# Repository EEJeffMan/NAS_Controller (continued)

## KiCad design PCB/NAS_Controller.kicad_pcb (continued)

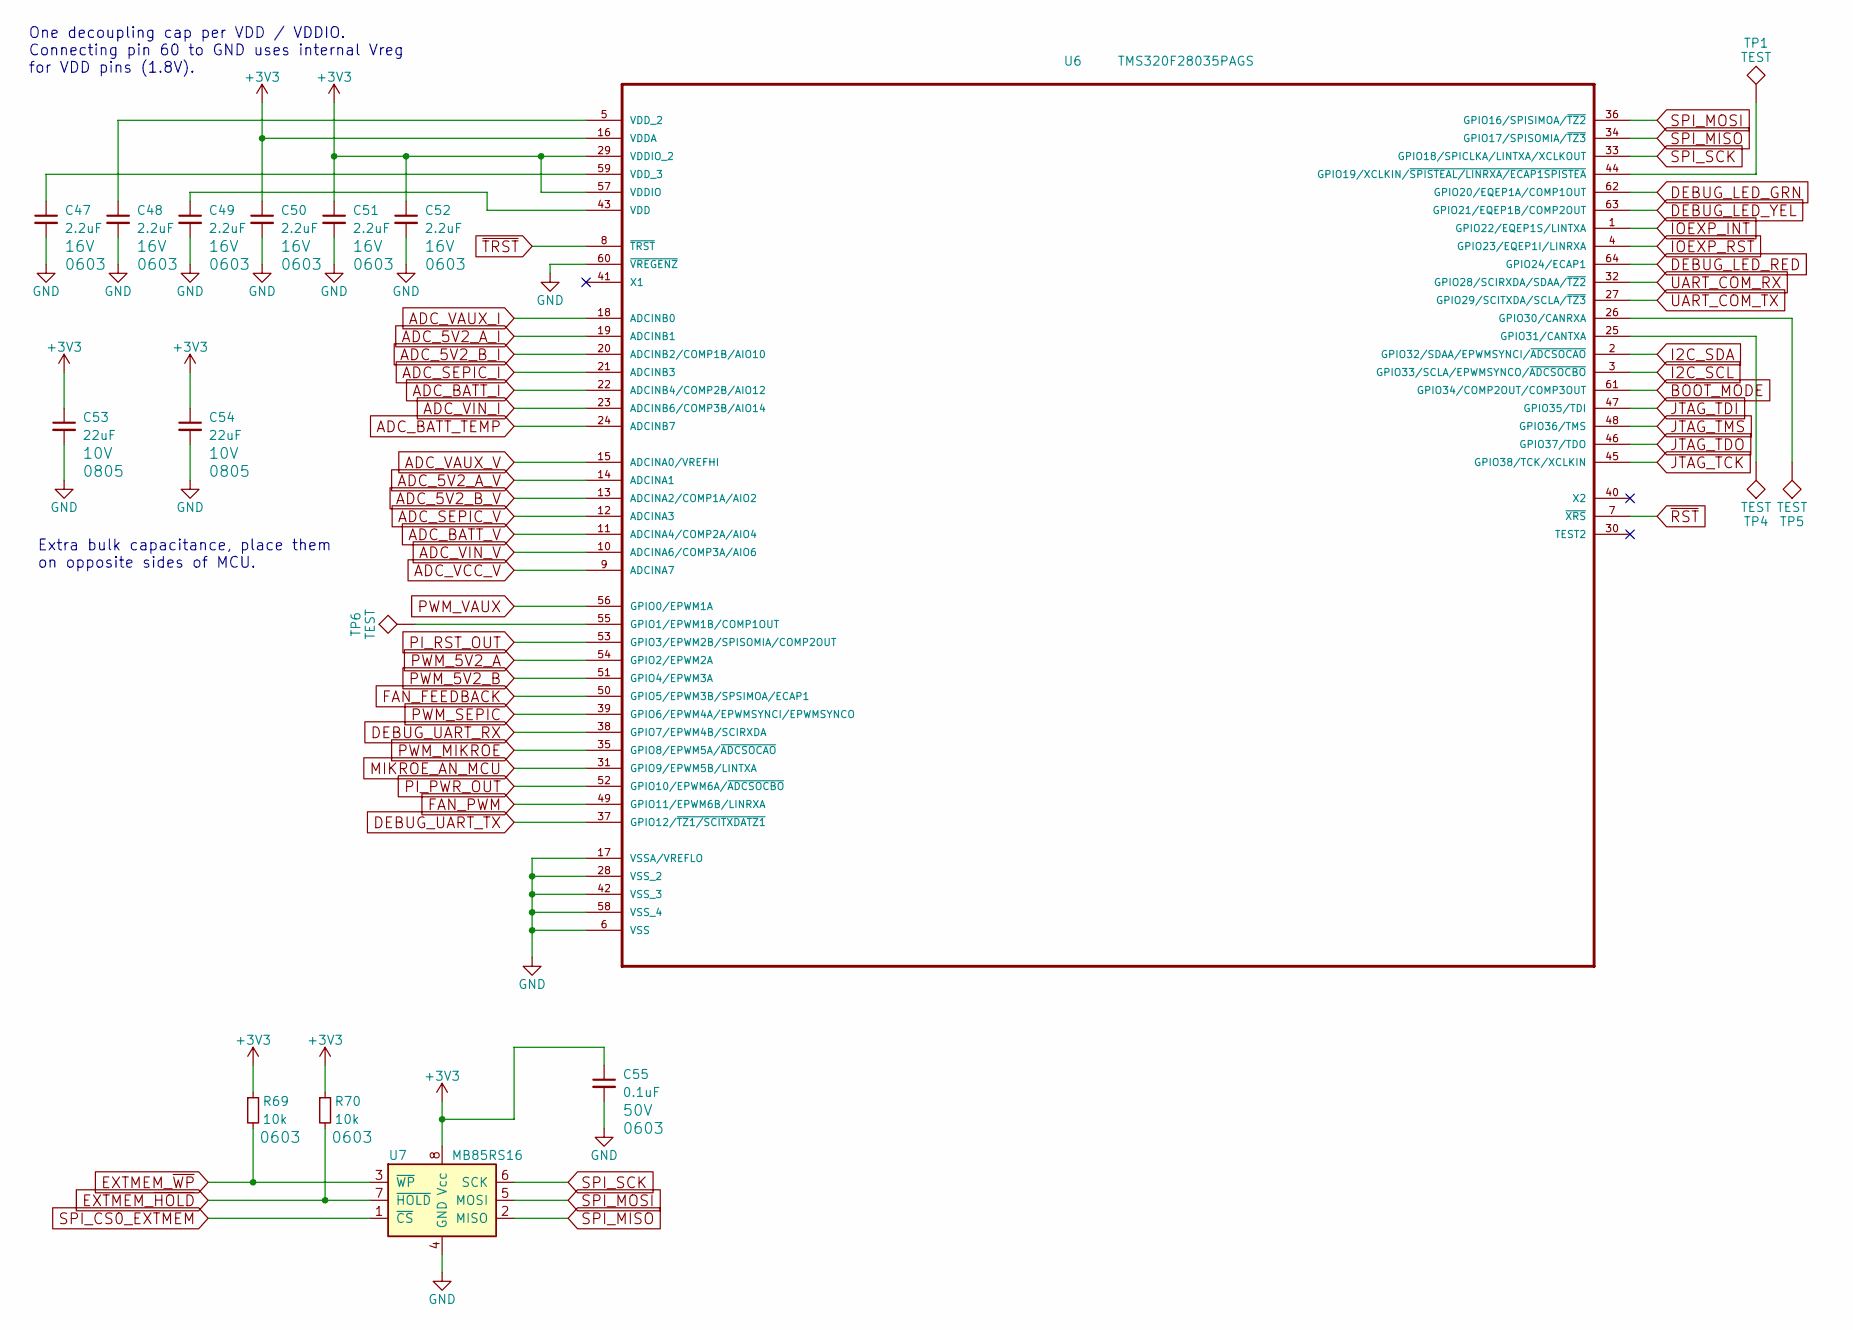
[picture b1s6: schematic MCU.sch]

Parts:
C47, C48, C49, C50, C51, C52: 2.2uF; C_0603; Voltage 16V
C53, C54: 22uF; C_0805; Voltage 10V
C55: 0.1uF; C_0603; Voltage 50V
R69, R70: 10k; R_0603
TP1, TP4, TP5, TP6: TEST; Measurement_Point_Round-SMD-Pad_Small
U6: TMS320F28035PAGS; QFP50P1200X1200X120-64N_PIN1
U7: MB85RS16; SOIC-8_W3.9mm

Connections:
+3V3: C50.1, C51.1, C52.1, C53.1, C54.1, C55.1, R69.1, R70.1, U6.16 (VDDA), U6.29 (VDDIO_2), U6.57 (VDDIO), U7.8 (Vcc); also elsewhere on the board
ADC_5V2_A_I: U6.19 (ADCINB1); also elsewhere on the board
ADC_5V2_A_V: U6.14 (ADCINA1); also elsewhere on the board
ADC_5V2_B_I: U6.20 (ADCINB2/COMP1B/AIO10); also elsewhere on the board
ADC_5V2_B_V: U6.13 (ADCINA2/COMP1A/AIO2); also elsewhere on the board
ADC_BATT_I: U6.22 (ADCINB4/COMP2B/AIO12); also elsewhere on the board
ADC_BATT_TEMP: U6.24 (ADCINB7); also elsewhere on the board
ADC_BATT_V: U6.11 (ADCINA4/COMP2A/AIO4); also elsewhere on the board
ADC_SEPIC_I: U6.21 (ADCINB3); also elsewhere on the board
ADC_SEPIC_V: U6.12 (ADCINA3); also elsewhere on the board
ADC_VAUX_I: U6.18 (ADCINB0); also elsewhere on the board
ADC_VAUX_V: U6.15 (ADCINA0/VREFHI); also elsewhere on the board
ADC_VCC_V: U6.9 (ADCINA7); also elsewhere on the board
ADC_VIN_I: U6.23 (ADCINB6/COMP3B/AIO14); also elsewhere on the board
ADC_VIN_V: U6.10 (ADCINA6/COMP3A/AIO6); also elsewhere on the board
BOOT_MODE: U6.61 (GPIO34/COMP2OUT/COMP3OUT); also elsewhere on the board
DEBUG_LED_GRN: U6.62 (GPIO20/EQEP1A/COMP1OUT); also elsewhere on the board
DEBUG_LED_RED: U6.64 (GPIO24/ECAP1); also elsewhere on the board
DEBUG_LED_YEL: U6.63 (GPIO21/EQEP1B/COMP2OUT); also elsewhere on the board
DEBUG_UART_RX: U6.38 (GPIO7/EPWM4B/SCIRXDA); also elsewhere on the board
DEBUG_UART_TX: U6.37 (GPIO12/~TZ1/SCITXDATZ1); also elsewhere on the board
ELOAD_PWM: TP6.1, U6.55 (GPIO1/EPWM1B/COMP1OUT); also elsewhere on the board
ELOAD_SEL: TP5.1, U6.26 (GPIO30/CANRXA); also elsewhere on the board
EXTMEM_~HOLD: R70.2, U7.7 (~HOLD); also elsewhere on the board
EXTMEM_~WP: R69.2, U7.3 (~WP); also elsewhere on the board
FAN_FEEDBACK: U6.50 (GPIO5/EPWM3B/SPSIMOA/ECAP1); also elsewhere on the board
FAN_PWM: U6.49 (GPIO11/EPWM6B/LINRXA); also elsewhere on the board
GND: C47.2, C48.2, C49.2, C50.2, C51.2, C52.2, C53.2, C54.2, C55.2, U6.6 (VSS), U6.17 (VSSA/VREFLO), U6.28 (VSS_2), U6.42 (VSS_3), U6.58 (VSS_4), U6.60 (~VREGENZ), U7.4 (GND); also elsewhere on the board
I2C_SCL: U6.3 (GPIO33/SCLA/EPWMSYNCO/~ADCSOCBO); also elsewhere on the board
I2C_SDA: U6.2 (GPIO32/SDAA/EPWMSYNCI/~ADCSOCAO); also elsewhere on the board
JTAG_TCK: U6.45 (GPIO38/TCK/XCLKIN); also elsewhere on the board
JTAG_TDI: U6.47 (GPIO35/TDI); also elsewhere on the board
JTAG_TDO: U6.46 (GPIO37/TDO); also elsewhere on the board
JTAG_TMS: U6.48 (GPIO36/TMS); also elsewhere on the board
MIKROE_AN_MCU: U6.31 (GPIO9/EPWM5B/LINTXA); also elsewhere on the board
unnamed: C47.1, U6.59 (VDD_3)
unnamed: C48.1, U6.5 (VDD_2)
unnamed: C49.1, U6.43 (VDD)
unnamed: TP1.1, U6.44 (GPIO19/XCLKIN/~SPISTEAL/LINRXA/ECAP1SPI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)
unnamed 186: U6.56 (GPIO0/EPWM1A); also elsewhere on the board
unnamed: TP4.1, U6.25 (GPIO31/CANTXA)
PI_PWR_OUT: U6.52 (GPIO10/EPWM6A/~ADCSOCBO); also elsewhere on the board
PI_RST_OUT: U6.53 (GPIO3/EPWM2B/SPISOMIA/COMP2OUT); also elsewhere on the board
PWM_5V2_A: U6.54 (GPIO2/EPWM2A); also elsewhere on the board
PWM_5V2_B: U6.51 (GPIO4/EPWM3A); also elsewhere on the board
PWM_MIKROE: U6.35 (GPIO8/EPWM5A/~ADCSOCAO); also elsewhere on the board
PWM_SEPIC: U6.39 (GPIO6/EPWM4A/EPWMSYNCI/EPWMSYNCO); also elsewhere on the board
SPI_CS0_EXTMEM: U7.1 (~CS); also elsewhere on the board
SPI_MISO: U6.34 (GPIO17/SPISOMIA/~TZ3), U7.2 (MISO); also elsewhere on the board
SPI_MOSI: U6.36 (GPIO16/SPISIMOA/~TZ2), U7.5 (MOSI); also elsewhere on the board
SPI_SCK: U6.33 (GPIO18/SPICLKA/LINTXA/XCLKOUT), U7.6 (SCK); also elsewhere on the board
UART_COM_RX: U6.32 (GPIO28/SCIRXDA/SDAA/~TZ2); also elsewhere on the board
UART_COM_TX: U6.27 (GPIO29/SCITXDA/SCLA/~TZ3); also elsewhere on the board
~IOEXP_INT: U6.1 (GPIO22/EQEP1S/LINTXA); also elsewhere on the board
~IOEXP_RST: U6.4 (GPIO23/EQEP1I/LINRXA); also elsewhere on the board
~RST: U6.7 (~XRS); also elsewhere on the board
~TRST: U6.8 (~TRST); also elsewhere on the board

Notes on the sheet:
One decoupling cap per VDD / VDDIO. Connecting pin 60 to GND uses internal Vreg for VDD pins (1.8V).
Extra bulk capacitance, place them on opposite sides of MCU.

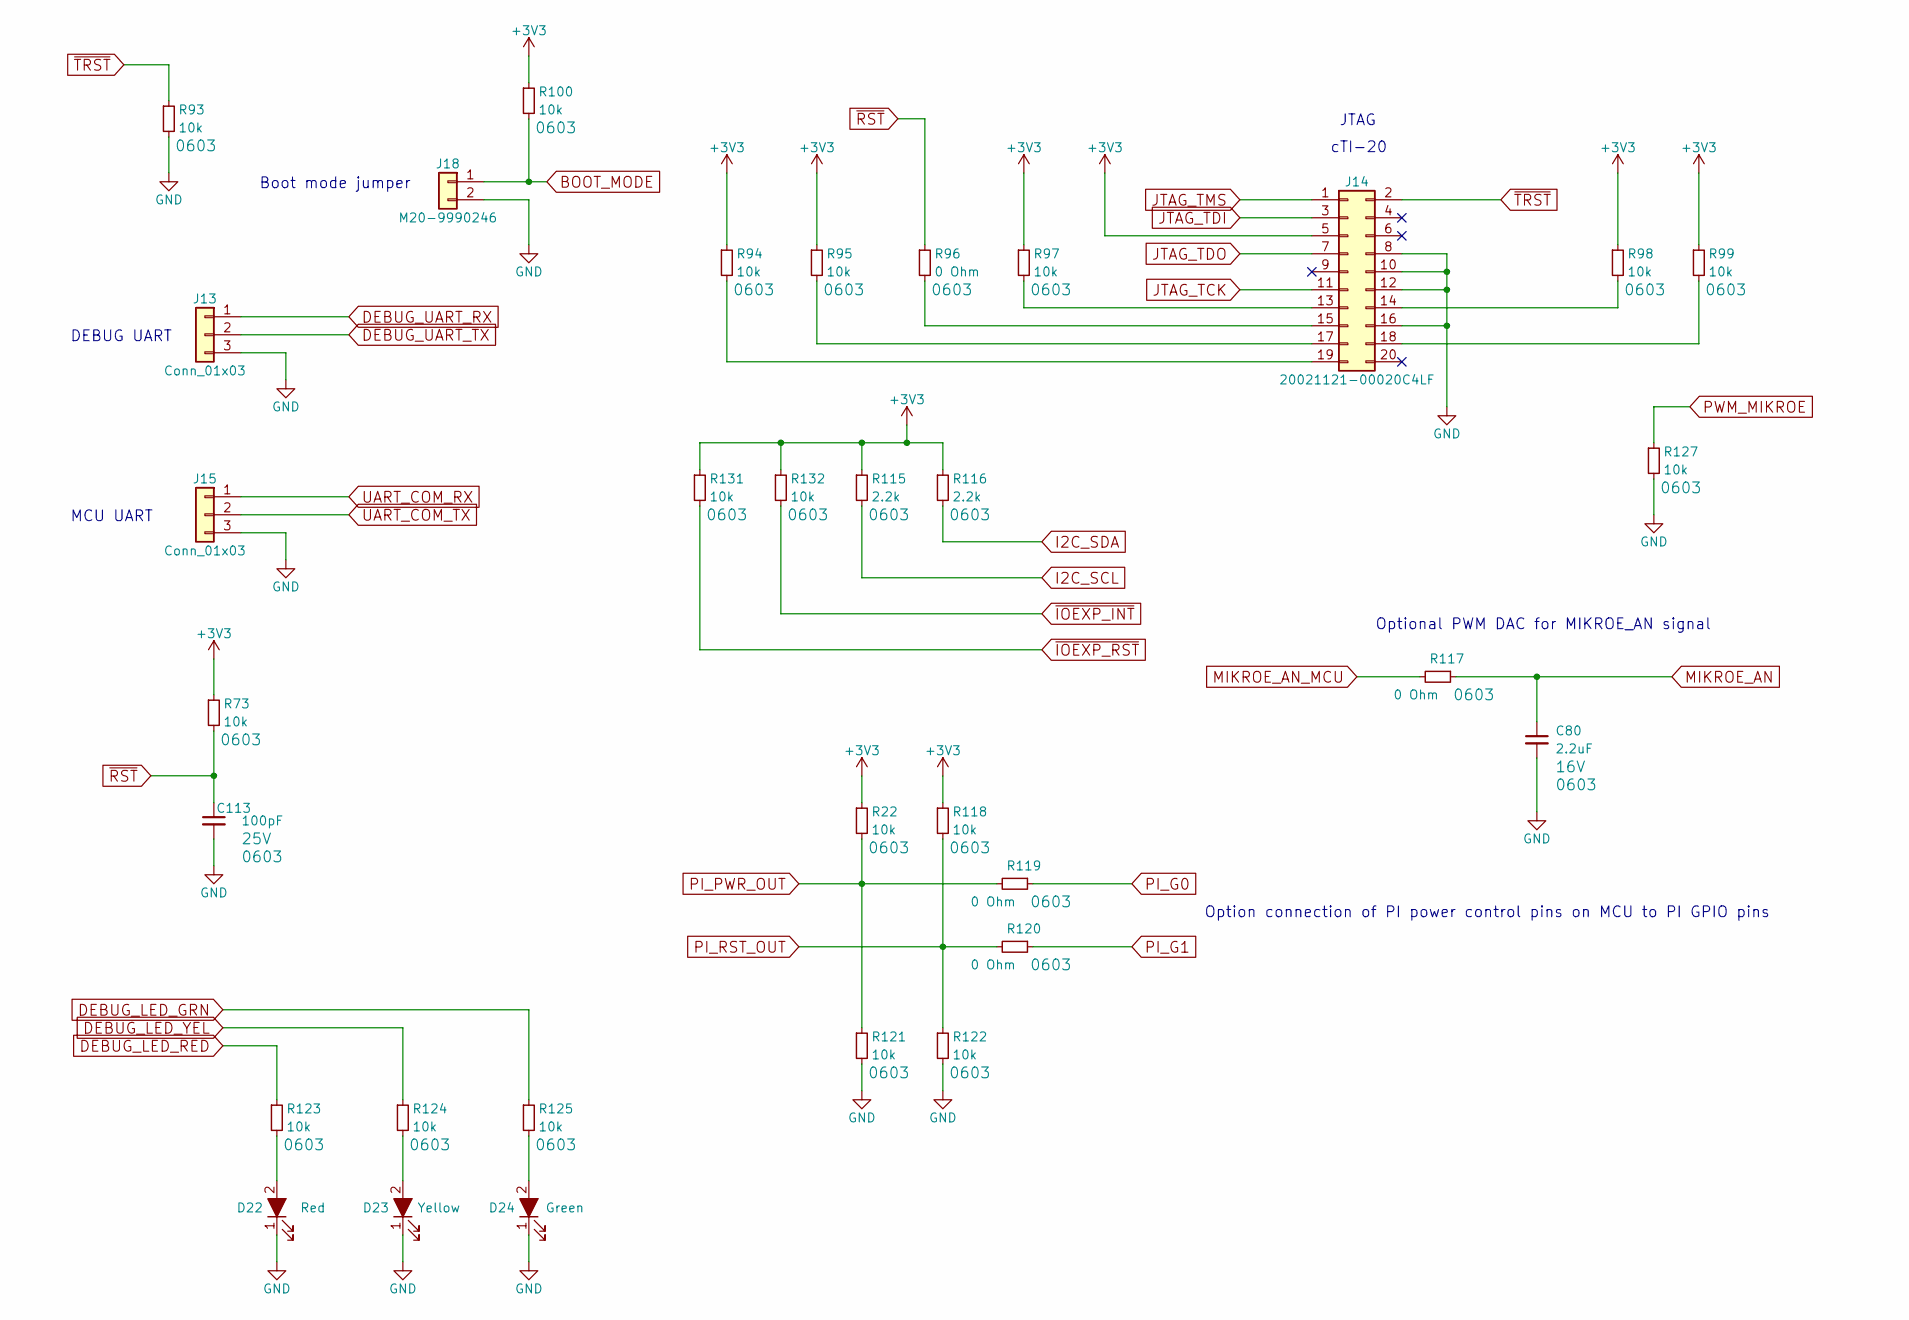
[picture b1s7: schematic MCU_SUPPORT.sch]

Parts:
C80: 2.2uF; C_0603; Voltage 16V
C113: 100pF; C_0603; Voltage 25V
D22: Red; LED_0603_HandSoldering
D23: Yellow; LED_0603_HandSoldering
D24: Green; LED_0603_HandSoldering
J13, J15: Conn_01x03; Pin_Header_Straight_1x03_Pitch2.54mm_SMD_Pin1Right
J14: 20021121-00020C4LF; Socket_Strip_Straight_2x10_Pitch1.27mm_SMD
J18: M20-9990246; Pin_Header_Straight_1x02_Pitch2.54mm
R22, R73, R93, R94, R95, R97, R98, R99, R100, R118, R121, R122, R123, R124, R125, R127, R131, R132: 10k; R_0603
R96, R117, R119, R120: 0 Ohm; R_0603
R115, R116: 2.2k; R_0603

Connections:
+3V3: J14.5, R22.1, R73.1, R94.1, R95.1, R97.1, R98.1, R99.1, R100.1, R115.1, R116.1, R118.1, R131.1, R132.1; also elsewhere on the board
BOOT_MODE: J18.1, R100.2; also elsewhere on the board
DEBUG_LED_GRN: R125.1; also elsewhere on the board
DEBUG_LED_RED: R123.1; also elsewhere on the board
DEBUG_LED_YEL: R124.1; also elsewhere on the board
DEBUG_UART_RX: J13.1; also elsewhere on the board
DEBUG_UART_TX: J13.2; also elsewhere on the board
GND: C80.2, C113.2, D22.1 (K), D23.1 (K), D24.1 (K), J13.3, J14.8, J14.10, J14.12, J14.16, J15.3, J18.2, R93.2, R121.2, R122.2, R127.2; also elsewhere on the board
I2C_SCL: R115.2; also elsewhere on the board
I2C_SDA: R116.2; also elsewhere on the board
JTAG_TCK: J14.11; also elsewhere on the board
JTAG_TDI: J14.3; also elsewhere on the board
JTAG_TDO: J14.7; also elsewhere on the board
JTAG_TMS: J14.1; also elsewhere on the board
MIKROE_AN: C80.1, R117.1; also elsewhere on the board
MIKROE_AN_MCU: R117.2; also elsewhere on the board
unnamed: D22.2 (A), R123.2
unnamed: D23.2 (A), R124.2
unnamed: D24.2 (A), R125.2
unnamed: J14.13, R97.2
unnamed: J14.14, R98.2
unnamed: J14.15, R96.2
unnamed: J14.17, R95.2
unnamed: J14.18, R99.2
unnamed: J14.19, R94.2
PI_G0: R119.1; also elsewhere on the board
PI_G1: R120.1; also elsewhere on the board
PI_PWR_OUT: R22.2, R119.2, R121.1; also elsewhere on the board
PI_RST_OUT: R118.2, R120.2, R122.1; also elsewhere on the board
PWM_MIKROE: R127.1; also elsewhere on the board
UART_COM_RX: J15.1; also elsewhere on the board
UART_COM_TX: J15.2; also elsewhere on the board
~IOEXP_INT: R132.2; also elsewhere on the board
~IOEXP_RST: R131.2; also elsewhere on the board
~RST: C113.1, R73.2, R96.1; also elsewhere on the board
~TRST: J14.2, R93.1; also elsewhere on the board

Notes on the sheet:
DEBUG UART
MCU UART
Boot mode jumper
JTAG
cTI-20
Optional PWM DAC for MIKROE_AN signal
Option connection of PI power control pins on MCU to PI GPIO pins

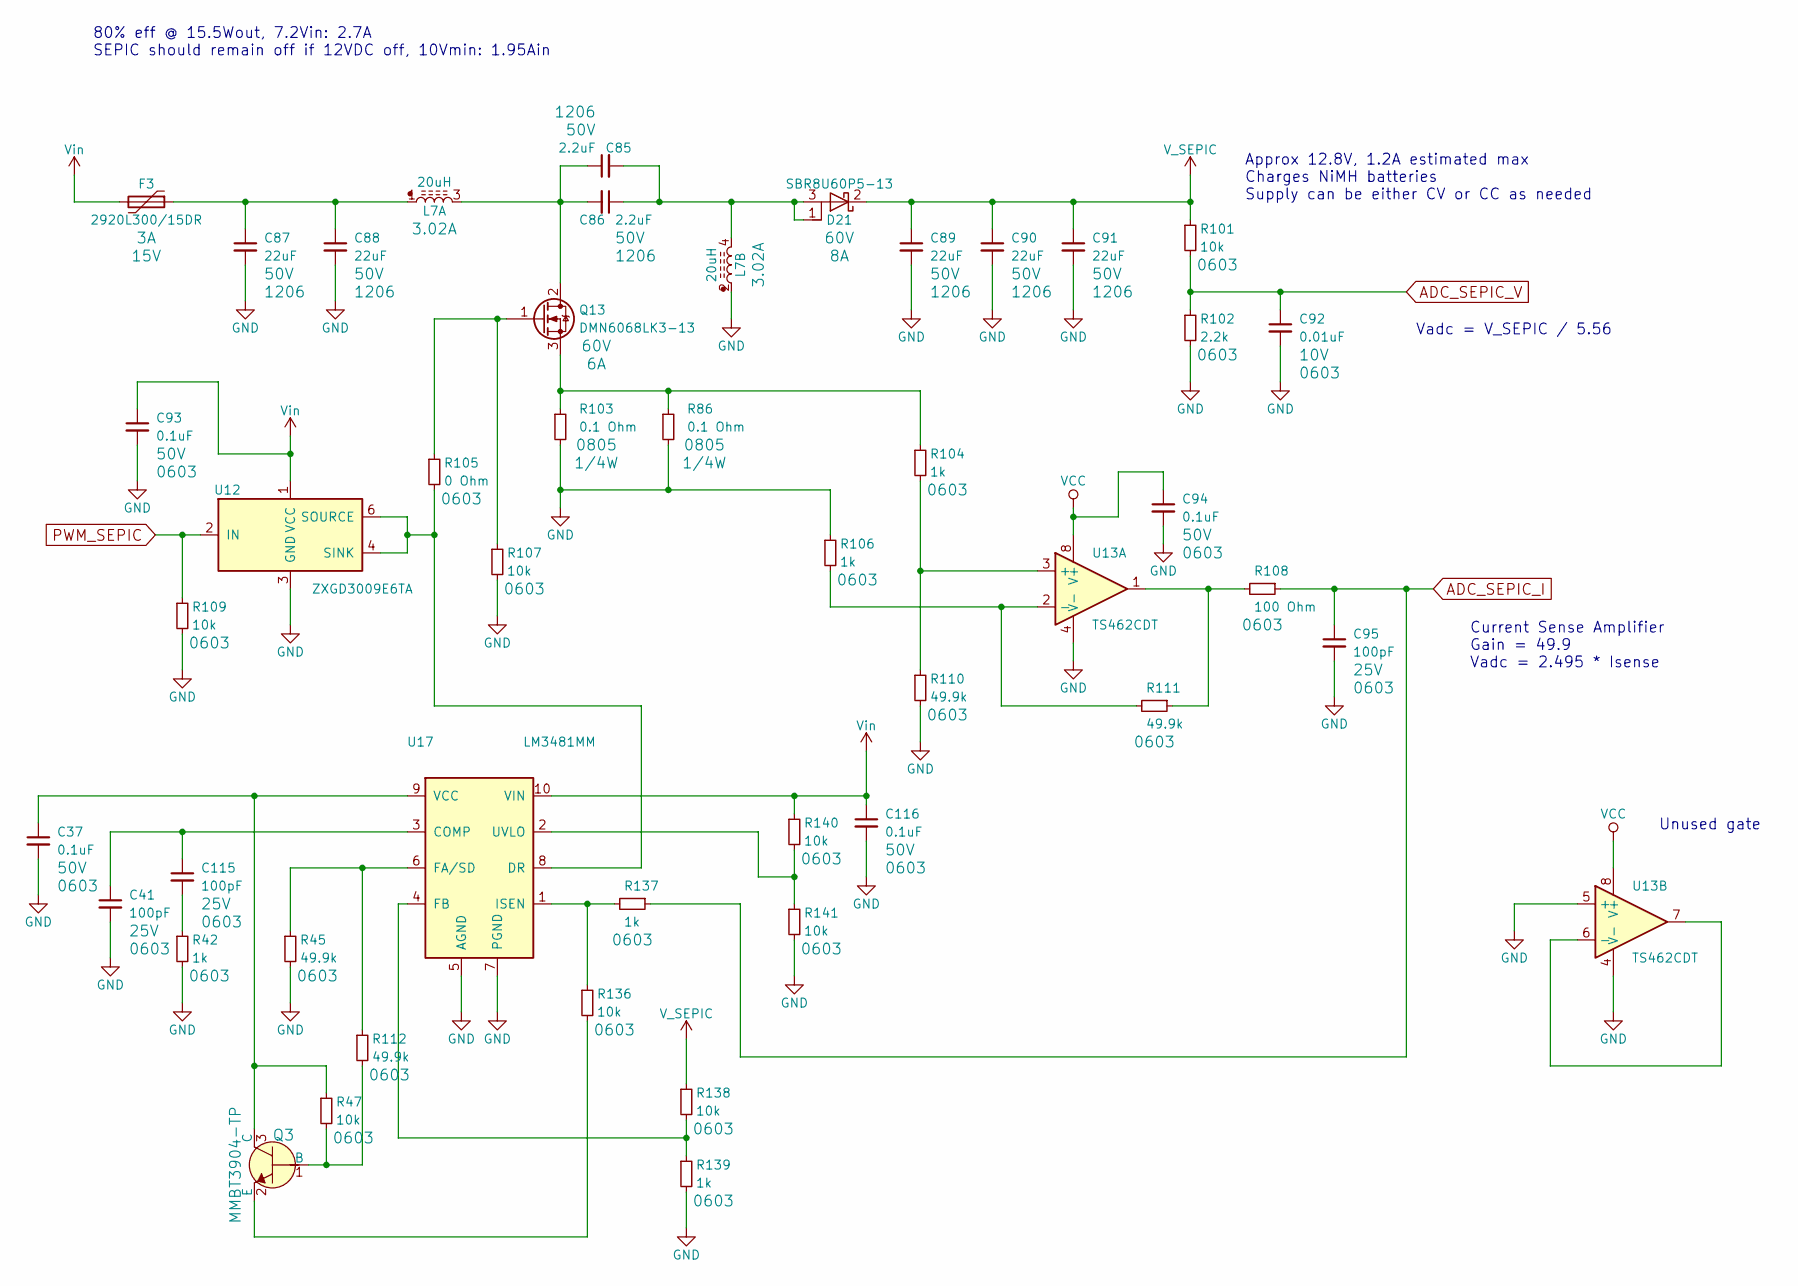
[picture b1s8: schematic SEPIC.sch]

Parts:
C37, C93, C94, C116: 0.1uF; C_0603; Voltage 50V
C41, C95, C115: 100pF; C_0603; Voltage 25V
C85, C86: 2.2uF; C_1206; Voltage 50V
C87, C88, C89, C90, C91: 22uF; C_1206; Voltage 50V
C92: 0.01uF; C_0603; Voltage 10V
D21: SBR8U60P5-13; Diodes_Incorporated_POWERDI_5; Voltage 60V
F3: 2920L300/15DR; 2920L; Voltage 15V
L7: 20uH; IND_C_12_5MMX12_5MM_HandSoldering
Q3: MMBT3904-TP; SOT-23-3; MPN MMBT3904-TP; Digi-Key_PN MMBT3904TPMSCT-ND
Q13: DMN6068LK3-13; TO-252-2; Voltage 60V
R42, R104, R106, R137, R139: 1k; R_0603
R45, R110, R111, R112: 49.9k; R_0603
R47, R101, R107, R109, R136, R138, R140, R141: 10k; R_0603
R86, R103: 0.1 Ohm; R_0805
R102: 2.2k; R_0603
R105: 0 Ohm; R_0603
R108: 100 Ohm; R_0603
U12: ZXGD3009E6TA; SOT-23-6
U13: TS462CDT; SOIC-8_W3.9mm
U17: LM3481MM; TSSOP-10_3x3mm_Pitch0.5mm

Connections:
ADC_SEPIC_I: C95.1, R108.1, R137.1; also elsewhere on the board
ADC_SEPIC_V: C92.1, R101.2, R102.1; also elsewhere on the board
GND: C37.2, C41.2, C87.2, C88.2, C89.2, C90.2, C91.2, C92.2, C93.2, C94.2, C95.2, C116.2, L7.2, R42.2, R45.2, R86.2, R102.2, R103.2, R106.1, R107.2, R109.2, R110.2, R139.2, R141.2, U12.3 (GND), U13.4 (V-), U13.5 (+), U17.5 (AGND), U17.7 (PGND); also elsewhere on the board
unnamed: C37.1, Q3.3 (C), R47.1, U17.9 (VCC)
unnamed: C85.1, C86.2, L7.3 (4), Q13.2 (D)
unnamed: C85.2, C86.1, D21.1 (A), D21.3 (A), L7.4
unnamed: C87.1, C88.1, F3.1, L7.1 (2)
unnamed: C41.1, C115.1, U17.3 (COMP)
unnamed: C115.2, R42.1
unnamed: Q3.1 (B), R47.2, R112.2
unnamed: Q3.2 (E), R136.2
unnamed: Q13.1 (G), R105.1, R107.1
unnamed: Q13.3 (S), R86.1, R103.1, R104.1
unnamed: R104.2, R110.1, U13.3 (+)
unnamed: R105.2, U12.4 (SINK), U12.6 (SOURCE), U17.8 (DR)
unnamed: R106.2, R111.2, U13.2 (-)
unnamed: R108.2, R111.1, U13.1
unnamed: R45.1, R112.1, U17.6 (FA/SD)
unnamed: R136.1, R137.2, U17.1 (ISEN)
unnamed: R138.2, R139.1, U17.4 (FB)
unnamed: R140.2, R141.1, U17.2 (UVLO)
unnamed: U13.6 (-), U13.7
PWM_SEPIC: R109.1, U12.2 (IN); also elsewhere on the board
VCC: C94.1, U13.8 (V+); also elsewhere on the board
V_SEPIC: C89.1, C90.1, C91.1, D21.2 (K), R101.1, R138.1; also elsewhere on the board
Vin: C93.1, C116.1, F3.2, R140.1, U12.1 (VCC), U17.10 (VIN); also elsewhere on the board

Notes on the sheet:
Approx 12.8V, 1.2A estimated max Charges NiMH batteries Supply can be either CV or CC as needed
Vadc = V_SEPIC / 5.56
Current Sense Amplifier Gain = 49.9 Vadc = 2.495 * Isense
Unused gate
80% eff @ 15.5Wout, 7.2Vin: 2.7A SEPIC should remain off if 12VDC off, 10Vmin: 1.95Ain

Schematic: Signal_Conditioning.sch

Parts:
C82, C83, C84, C98: 0.1uF; C_0603; Voltage 50V
D14, D15, D16, D17, D18, D19, D20: BAS40BRW-7-F; SOT-363_SC-70-6
R88, R89, R90, R91, R92: 10k; R_0603
U9, U10: TS5A3357DCUR; VSSOP-8_2.3x2mm_Pitch0.5mm
U11: PCA6416APW,118; SSOP-24_5.3x8.2mm_Pitch0.65mm

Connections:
+3V3: C82.1, C83.1, C84.1, C98.1, R88.1, R89.1, U9.8 (V+), U10.8 (V+), U11.2 (VDD(power)), U11.24 (VDD(bus)); also elsewhere on the board
ADC_5V2_A_I: D18.6 (common); also elsewhere on the board
ADC_5V2_A_V: D16.3 (common); also elsewhere on the board
ADC_5V2_B_I: D18.3 (common); also elsewhere on the board
ADC_5V2_B_V: D16.6 (common); also elsewhere on the board
ADC_BATT_I: D19.3 (common); also elsewhere on the board
ADC_BATT_TEMP: D20.3 (common); also elsewhere on the board
ADC_BATT_V: D15.6 (common); also elsewhere on the board
ADC_SEPIC_I: D19.6 (common); also elsewhere on the board
ADC_SEPIC_V: D15.3 (common); also elsewhere on the board
ADC_VAUX_I: D17.3 (common); also elsewhere on the board
ADC_VAUX_V: D17.6 (common); also elsewhere on the board
ADC_VCC_V: D14.6 (common); also elsewhere on the board
ADC_VIN_I: D20.6 (common); also elsewhere on the board
ADC_VIN_V: D14.3 (common); also elsewhere on the board
EXTMEM_~HOLD: U11.11 (P0_7); also elsewhere on the board
EXTMEM_~WP: U11.5 (P0_1); also elsewhere on the board
GND: C82.2, C83.2, C84.2, C98.2, D14.1 (A), D14.2 (A), D15.1 (A), D15.2 (A), D16.1 (A), D16.2 (A), D17.1 (A), D17.2 (A), D18.1 (A), D18.2 (A), D19.1 (A), D19.2 (A), D20.1 (A), D20.2 (A), R90.2, R91.2, R92.2, U9.4 (GND), U10.4 (GND), U11.12 (VSS); also elsewhere on the board
I2C_SCL: U11.22 (SCL); also elsewhere on the board
I2C_SDA: U11.23 (SDA); also elsewhere on the board
MIKROE_INT: U11.14 (P1_1); also elsewhere on the board
MIKROE_RST: U11.13 (P1_0); also elsewhere on the board
MUX_UART_S0: R88.2, R90.1, U9.6 (IN1), U10.6 (IN1), U11.7 (P0_3); also elsewhere on the board
MUX_UART_S1: R89.2, R91.1, U9.5 (IN2), U10.5 (IN2), U11.8 (P0_4); also elsewhere on the board
unnamed: R92.1, U11.21 (ADDR)
PI_G0: U11.15 (P1_2); also elsewhere on the board
PI_G1: U11.16 (P1_3); also elsewhere on the board
PI_G2: U11.17 (P1_4); also elsewhere on the board
PI_G3: U11.18 (P1_5); also elsewhere on the board
PWR_SW_IN: U11.20 (P1_7); also elsewhere on the board
RST_SW_IN: U11.6 (P0_2); also elsewhere on the board
SPI_CS0_EXTMEM: U11.9 (P0_5); also elsewhere on the board
SPI_CS1_MIKROE: U11.10 (P0_6); also elsewhere on the board
UART_COM_RX: U10.7 (COM); also elsewhere on the board
UART_COM_TX: U9.7 (COM); also elsewhere on the board
UART_MIKROE_RX: U10.2 (NO1); also elsewhere on the board
UART_MIKROE_TX: U9.2 (NO1); also elsewhere on the board
UART_PI_RX: U10.1 (NO0); also elsewhere on the board
UART_PI_TX: U9.1 (NO0); also elsewhere on the board
UART_XBEE_RX: U10.3 (NO2); also elsewhere on the board
UART_XBEE_TX: U9.3 (NO2); also elsewhere on the board
USB_RST: U11.4 (P0_0); also elsewhere on the board
VCLAMP: D14.4 (K), D14.5 (K), D15.4 (K), D15.5 (K), D16.4 (K), D16.5 (K), D17.4 (K), D17.5 (K), D18.4 (K), D18.5 (K), D19.4 (K), D19.5 (K), D20.4 (K), D20.5 (K); also elsewhere on the board
XBEE_RST: U11.19 (P1_6); also elsewhere on the board
~IOEXP_INT: U11.1 (~INT); also elsewhere on the board
~IOEXP_RST: U11.3 (~RESET); also elsewhere on the board

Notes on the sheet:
I/O Expander
MUX a single UART from MCU to 3 destinations
Clamp all ADC inputs to protect MCU

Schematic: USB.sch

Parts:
C62, C63: 2.2uF; C_0603; Voltage 16V
C64, C65, C66, C67, C70, C71: 0.1uF; C_0603; Voltage 50V
C68, C69: 33pF; C_0603; Voltage 50V
Q4: 2N7002; SOT-23
R74, R75, R77, R78: 100k; R_0603
R76, R79, R80, R81, R128: 10k; R_0603
R134: 649 Ohm; R_0603
U8: CY7C65634-48AXCT; LQFP-48_7x7mm_Pitch0.5mm
Y1: 12MHz; Crystal_SMD_HC49-SD

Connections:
+3V3: C62.1, C63.1, C64.1, C65.1, C66.1, C67.1, C70.1, C71.1, R74.1, R75.1, R76.1, R79.1, R80.1, U8.1 (VCC_A), U8.7 (VCC_A), U8.12 (VCC_A), U8.16 (VCC_A), U8.34 (VCC_D), U8.38 (VCC_D); also elsewhere on the board
GND: C62.2, C63.2, C64.2, C65.2, C66.2, C67.2, C68.2, C69.2, C70.2, C71.2, Q4.2 (S), R77.2, R78.2, R81.2, R128.2, R134.2, U8.2 (GND), U8.8 (GND), U8.13 (GND), U8.20 (GND); also elsewhere on the board
unnamed: C68.1, U8.14 (XIN), Y1.1
unnamed: C69.1, U8.15 (XOUT), Y1.2
unnamed: R74.2, R77.1, U8.9 (USB_DN2-)
unnamed: R75.2, R78.1, U8.10 (USB_DN2+)
unnamed: R76.2, U8.37 (SELFPWR)
unnamed: R79.2, U8.44 (SEL27)
unnamed: R80.2, U8.25 (SEL48)
unnamed: R81.1, U8.39 (GANG)
unnamed: R134.1, U8.11 (RREF)
USB_DN_N: U8.5 (USB_DN1-); also elsewhere on the board
USB_DN_P: U8.6 (USB_DN1+); also elsewhere on the board
USB_RST: Q4.1 (G), R128.1; also elsewhere on the board
USB_UP_N: U8.3 (USB_UP-); also elsewhere on the board
USB_UP_P: U8.4 (USB_UP+); also elsewhere on the board
USB_VBUS_DET: Q4.3 (D), U8.26 (~RESET); also elsewhere on the board

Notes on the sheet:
Optional pullup / pulldowns for unused port
Pins 12 & 16 get 1 2.2uF and 1 0.1uF, all other VCC_x pins get a 0.1uF

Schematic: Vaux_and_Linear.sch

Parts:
C10, C11: 22uF; C_1206; Voltage 50V
C12, C13: 22uF; C_0805; Voltage 10V
C14, C20: 0.01uF; C_0603; Voltage 10V
C15: 1uF; C_0603; Voltage 50V
C16: 100pF; C_0603; Voltage 25V
C18, C19: 2.2uF; C_0603; Voltage 16V
C23: 0.1uF; C_0603; Voltage 50V
D4: 4.7V; D_SOD-123
D9: 3.3V; D_SOD-123
J12: Conn_01x03; Pin_Header_Straight_1x03_Pitch2.54mm_SMD_Pin1Right
L1: 1uH; INDP2622X120N
L2: 47uH; Inductor_Taiyo-Yuden_NR-80xx_HandSoldering
R8: 0.1 Ohm; R_0805
R9, R11, R12, R19, R21: 10k; R_0603
R10: 100k; R_0603
R13, R14: 2.2k; R_0603
R15: 2.49k; R_0603
R16: 100 Ohm; R_0603
R17, R18: 49.9k; R_0603
R23: 1k; R_0603
R142: 0 Ohm; R_0603
U2: TS462CDT; SOIC-8_W3.9mm
U3: AZ1084CD-3.3; TO-252-2
U14: AP65211AWU-7; SOT-23-6_Handsoldering

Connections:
+3V3: C19.1, U3.2 (VO); also elsewhere on the board
ADC_VAUX_I: C16.1, R16.1; also elsewhere on the board
ADC_VAUX_V: C14.1, R9.2, R11.1; also elsewhere on the board
ADC_VCC_V: C20.1, R19.2, R21.1; also elsewhere on the board
GND: C10.2, C11.2, C12.2, C13.2, C14.2, C16.2, C18.2, C19.2, C20.2, C23.2, D4.2 (A), D9.2 (A), J12.3, R11.2, R15.2, R17.2, R21.2, U2.4 (V-), U3.1 (GND), U14.1 (GND); also elsewhere on the board
unnamed: C11.1, L1.2, R10.1, U14.3 (IN)
unnamed: C15.1, U14.6 (BST)
unnamed: C15.2, L2.1, U14.2 (SW)
unnamed: D4.1 (K), R10.2, U14.5 (EN)
unnamed: L2.2, R8.1, R13.1
unnamed: R12.2, R15.1, U14.4 (FB)
unnamed: R13.2, R17.1, U2.5 (+)
unnamed: R14.2, R18.2, U2.6 (-)
unnamed: R16.2, R18.1, U2.7
VCC: R19.1, R142.1, U2.8 (V+); also elsewhere on the board
VCLAMP: C23.1, D9.1 (K), R23.2; also elsewhere on the board
Vaux: C12.1, C13.1, C18.1, J12.1, J12.2, R8.2, R9.1, R12.1, R14.1, R23.1, R142.2, U3.3 (VI)
Vin: C10.1, L1.1; also elsewhere on the board

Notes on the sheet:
VCC approx 4.5V -Startup supply for 3V3 (startup will be approx 3.9V) -Supply for op amps
VAUX approx 5V, 1A estimated max More efficient source for 3V3 and VCC
Current Sense Amplifier Gain = 22.7 Vadc = 2.27 * Isense
Vadc = Vaux / 2
90% eff @ 5Wout, 7.2Vin: 770mAin

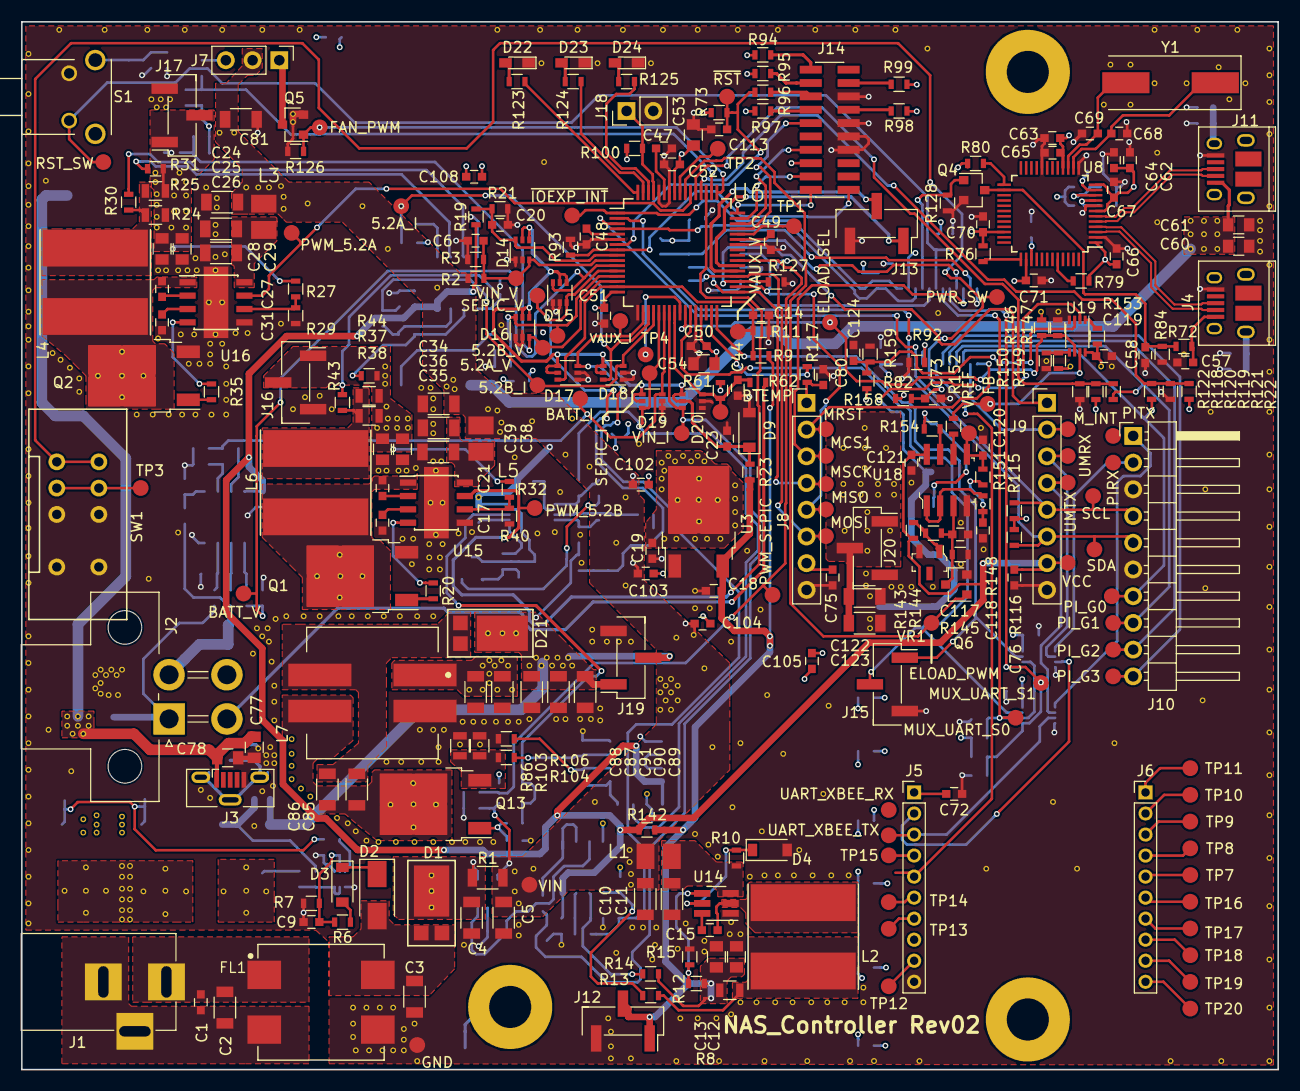
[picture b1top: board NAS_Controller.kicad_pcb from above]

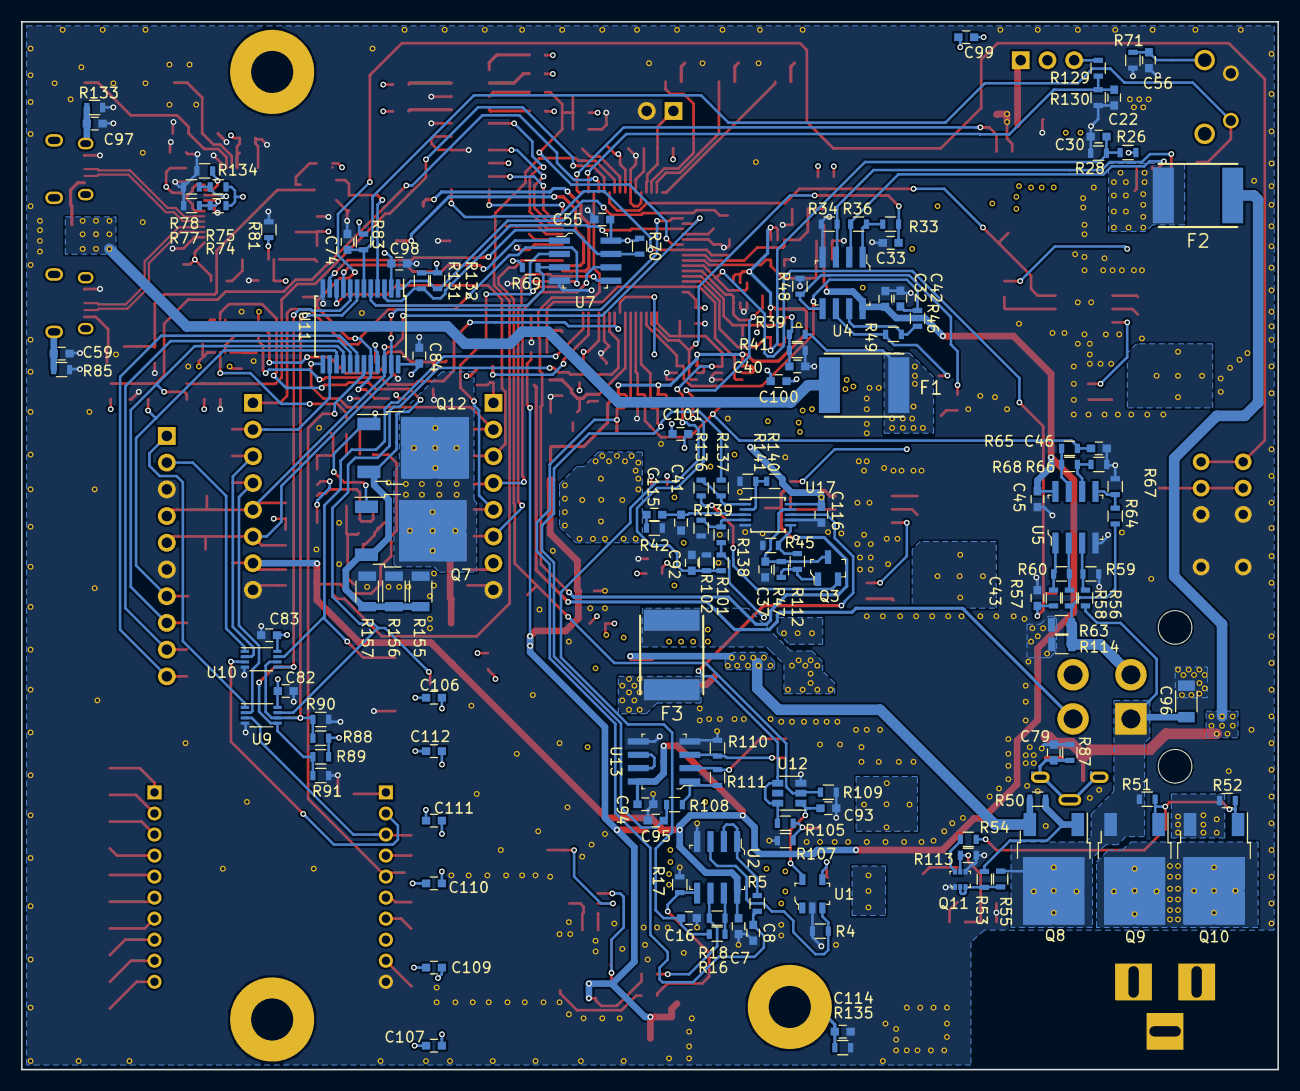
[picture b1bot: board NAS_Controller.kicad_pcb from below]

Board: 4 copper layers, 119.5 x 99.6 mm, 433 parts (139 on the bottom side), 220 nets.

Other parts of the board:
5.2A_I, 5.2A_V, 5.2B_I, 5.2B_V: Measurement_Point_Round-SMD-Pad_Small
BATT_I: Measurement_Point_Round-SMD-Pad_Small
BATT_V: Measurement_Point_Round-SMD-Pad_Small
BTEMP: Measurement_Point_Round-SMD-Pad_Small
ELOAD_PWM: Measurement_Point_Round-SMD-Pad_Small
ELOAD_SEL: Measurement_Point_Round-SMD-Pad_Small
FAN_PWM: Measurement_Point_Round-SMD-Pad_Small
FB: Measurement_Point_Round-SMD-Pad_Small
GND: Measurement_Point_Round-SMD-Pad_Small
J19: Conn_01x03; Pin_Header_Straight_1x03_Pitch2.54mm_SMD_Pin1Right
MCS1: Measurement_Point_Round-SMD-Pad_Small
MISO: Measurement_Point_Round-SMD-Pad_Small
MK1#2, MK1#3: Mounting_Hole_PAD; MountingHole_4mm_Pad
MOSI: Measurement_Point_Round-SMD-Pad_Small
MRST: Measurement_Point_Round-SMD-Pad_Small
MSCK: Measurement_Point_Round-SMD-Pad_Small
MUX_UART_S0, MUX_UART_S1: Measurement_Point_Round-SMD-Pad_Small
M_INT: Measurement_Point_Round-SMD-Pad_Small
PIRX: Measurement_Point_Round-SMD-Pad_Small
PITX: Measurement_Point_Round-SMD-Pad_Small
PI_G0, PI_G1, PI_G2, PI_G3: Measurement_Point_Round-SMD-Pad_Small
PWM_5.2A, PWM_5.2B: Measurement_Point_Round-SMD-Pad_Small
PWM_SEPIC: Measurement_Point_Round-SMD-Pad_Small
PWR_SW: Measurement_Point_Round-SMD-Pad_Small
RST_SW: Measurement_Point_Round-SMD-Pad_Small
SCL: Measurement_Point_Round-SMD-Pad_Small
SDA: Measurement_Point_Round-SMD-Pad_Small
SEPIC_I: Measurement_Point_Round-SMD-Pad_Small
SEPIC_V: Measurement_Point_Round-SMD-Pad_Small
TP2: TEST; Measurement_Point_Round-SMD-Pad_Small
UART_XBEE_RX: Measurement_Point_Round-SMD-Pad_Small
UART_XBEE_TX: Measurement_Point_Round-SMD-Pad_Small
UMRX: Measurement_Point_Round-SMD-Pad_Small
UMTX: Measurement_Point_Round-SMD-Pad_Small
VAUX_I: Measurement_Point_Round-SMD-Pad_Small
VAUX_V: Measurement_Point_Round-SMD-Pad_Small
VCC: Measurement_Point_Round-SMD-Pad_Small
VIN: Measurement_Point_Round-SMD-Pad_Small
VIN_I: Measurement_Point_Round-SMD-Pad_Small
VIN_V: Measurement_Point_Round-SMD-Pad_Small
VREF: Measurement_Point_Round-SMD-Pad_Small

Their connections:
ADC_5V2_A_I: 5.2A_I.1; also elsewhere on the board
ADC_5V2_A_V: 5.2A_V.1; also elsewhere on the board
ADC_5V2_B_I: 5.2B_I.1; also elsewhere on the board
ADC_5V2_B_V: 5.2B_V.1; also elsewhere on the board
ADC_BATT_I: BATT_I.1; also elsewhere on the board
ADC_BATT_TEMP: BTEMP.1; also elsewhere on the board
ADC_BATT_V: BATT_V.1; also elsewhere on the board
ADC_SEPIC_I: SEPIC_I.1; also elsewhere on the board
ADC_SEPIC_V: SEPIC_V.1; also elsewhere on the board
ADC_VAUX_I: VAUX_I.1; also elsewhere on the board
ADC_VAUX_V: VAUX_V.1; also elsewhere on the board
ADC_VIN_I: VIN_I.1; also elsewhere on the board
ADC_VIN_V: VIN_V.1; also elsewhere on the board
ELOAD_PWM: ELOAD_PWM.1; also elsewhere on the board
ELOAD_SEL: ELOAD_SEL.1; also elsewhere on the board
FAN_PWM: FAN_PWM.1; also elsewhere on the board
GND: GND.1, J19.3; also elsewhere on the board
I2C_SCL: SCL.1; also elsewhere on the board
I2C_SDA: SDA.1; also elsewhere on the board
MIKROE_INT: M_INT.1; also elsewhere on the board
MIKROE_RST: MRST.1; also elsewhere on the board
MUX_UART_S0: MUX_UART_S0.1; also elsewhere on the board
MUX_UART_S1: MUX_UART_S1.1; also elsewhere on the board
unnamed 74: MK1#3.1; also elsewhere on the board
unnamed 79: VREF.1; also elsewhere on the board
unnamed 181: FB.1; also elsewhere on the board
unnamed 186: TP2.1; also elsewhere on the board
PI_G0: PI_G0.1; also elsewhere on the board
PI_G1: PI_G1.1; also elsewhere on the board
PI_G2: PI_G2.1; also elsewhere on the board
PI_G3: PI_G3.1; also elsewhere on the board
PWM_5V2_A: PWM_5.2A.1; also elsewhere on the board
PWM_5V2_B: PWM_5.2B.1; also elsewhere on the board
PWM_SEPIC: PWM_SEPIC.1; also elsewhere on the board
PWR_SW_IN: PWR_SW.1; also elsewhere on the board
RST_SW_IN: RST_SW.1; also elsewhere on the board
SPI_CS1_MIKROE: MCS1.1; also elsewhere on the board
SPI_MISO: MISO.1; also elsewhere on the board
SPI_MOSI: MOSI.1; also elsewhere on the board
SPI_SCK: MSCK.1; also elsewhere on the board
UART_MIKROE_RX: UMRX.1; also elsewhere on the board
UART_MIKROE_TX: UMTX.1; also elsewhere on the board
UART_XBEE_TX: UART_XBEE_TX.1; also elsewhere on the board
VCC: VCC.1; also elsewhere on the board
V_SEPIC: J19.1, J19.2; also elsewhere on the board
Vin: VIN.1; also elsewhere on the board
